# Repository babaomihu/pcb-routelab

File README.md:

# PCB RouteLab

[中文说明](README.zh-CN.md)

PCB RouteLab is a research toolkit for **running, inspecting and comparing PCB routing strategies** on KiCad boards. It packages an existing Harness-based research project into isolated, reproducible jobs.

- Run native routing on a copy of a board and its project rules.
- Inspect native planning observations and execute fixed multi-net order/layer/corridor plans.
- Evaluate bounded congestion-update expressions without executing arbitrary generated code.
- Optionally let DeepSeek Harness orchestrate diagnostic and routing tools.
- Review a separate candidate, a copper change list and a native KiCad acceptance report before export.
- Run in the foreground or background; inspect status and cancel a job.

## Quick start

Native execution is validated on **macOS arm64, KiCad 10.0.4 and Python 3.13**. Install KiCad and a Rust toolchain first. Core operation does not require model configuration.

```sh
python3.13 -m venv .venv
.venv/bin/python -m pip install -r requirements-build.lock.txt -r requirements.lock.txt
.venv/bin/python -m pip install --no-build-isolation --no-deps .
.venv/bin/pcb-routelab build-engine --build-dir ../routelab-build
.venv/bin/pcb-routelab doctor
.venv/bin/pcb-routelab run --board examples/two-nets/two-nets.kicad_pcb --output ../routelab-example
.venv/bin/pcb-routelab export ../routelab-example --output ../routelab-export
```

Every output directory must be new. A matching `.kicad_pro` is required; use `--project PATH` when it is elsewhere. Adjacent `.kicad_dru`/legacy `.pro` files are copied and checked. Custom rule programs are currently rejected by the generation contract. The tool does not clear copper or silently simplify unsupported input.

## Supported inputs and results

The release targets modern, two-copper-layer boards with supported ordinary pads, straight tracks and through vias. Zones, copper arcs, custom pads, unstable object identities and legacy imports are rejected. Full details: [support boundary](docs/SUPPORT.md).

`success` means connections improved to completion and the original-rule audit passed. `safe_incomplete` means a verified partial improvement. `no_progress`, `rejected`, `timeout`, `cancelled` and `error` remain distinct. Existing DRC errors may remain; they are reported and compared individually. Success is not manufacturing sign-off. Only accepted improving candidates can be exported, with another audit at export.

## Documentation

- [Installation and native build](docs/INSTALL.md)
- [Routing, planning, policy and model commands](docs/USAGE.md)
- [Scope and limitations](docs/SUPPORT.md)
- [Offline release validation](docs/VALIDATION.md)
- [Research results and reusable components](docs/RESEARCH.md)
- [Troubleshooting](docs/TROUBLESHOOTING.md)
- [Source attribution](THIRD_PARTY_NOTICES.md)

Examples, aggregate research results and offline release checks are available under `examples/` and `evidence/`.

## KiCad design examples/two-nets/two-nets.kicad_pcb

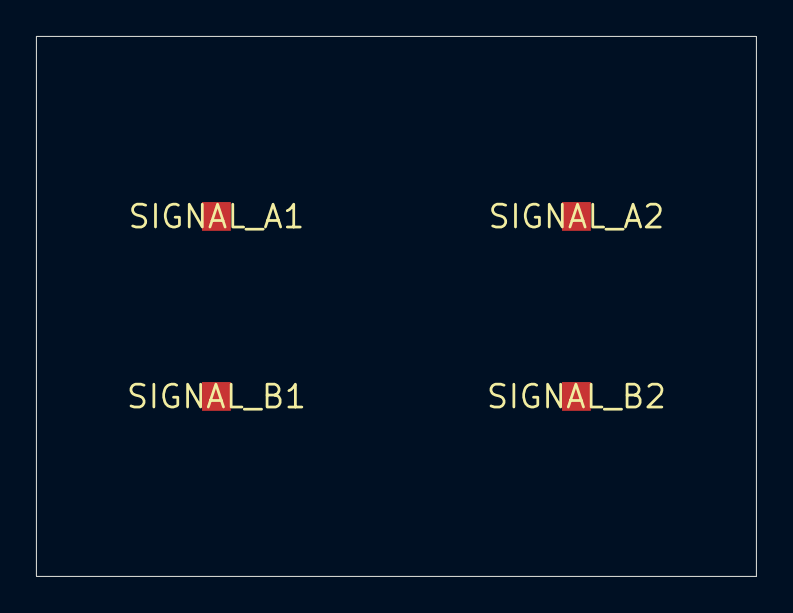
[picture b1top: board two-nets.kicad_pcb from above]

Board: 2 copper layers, 40.0 x 30.0 mm, 4 parts (0 on the bottom side), 2 nets, no tracks yet.

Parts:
SIGNAL_A1, SIGNAL_A2: RouteLab fixture
SIGNAL_B1, SIGNAL_B2: RouteLab fixture

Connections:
SIGNAL_A: SIGNAL_A1.1, SIGNAL_A2.1
SIGNAL_B: SIGNAL_B1.1, SIGNAL_B2.1
